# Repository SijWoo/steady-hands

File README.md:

# Introduction
This repo contains the src files and hardware for a wearable wrist band that treats chronic shaky hands.

## Background
Tremors make your hands or other parts of your body involuntarily move and shake. Severe cases can even make everday tasks difficult. This device is to let people from mild to severe cases regain control through the use of vibration feedback.

## How it works
Overloading the sensory nerves can surpress the involuntary movement. Vibration motors are implemented inside the wearable to constantly stimulate the nerves.

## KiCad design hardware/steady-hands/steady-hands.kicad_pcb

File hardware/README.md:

# Hardware
Descriptions and explanations

## Components
| Description | P/N |
| --- | --- |
| Microcontroller | STM32F411CE |
| Vibrating Motors | |
| IMU | BNO055 |

## Microcontroller
The STM32f411CE controls the vibration motors.

## Vibrating Motors
Small motors for phones are repurposed for this project. A transistor interface is needed to drive the required current.

## IMU
The BNO055 uses the I2C interface.

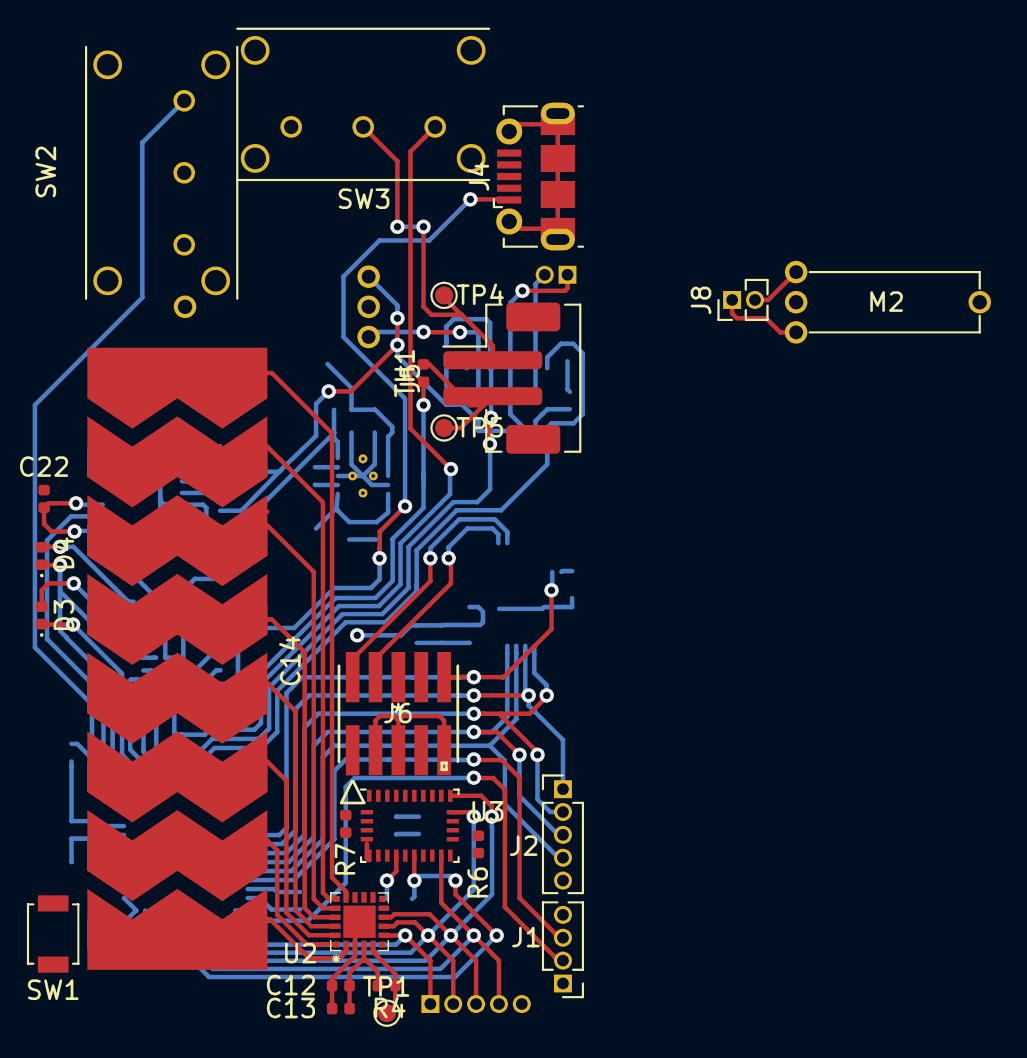
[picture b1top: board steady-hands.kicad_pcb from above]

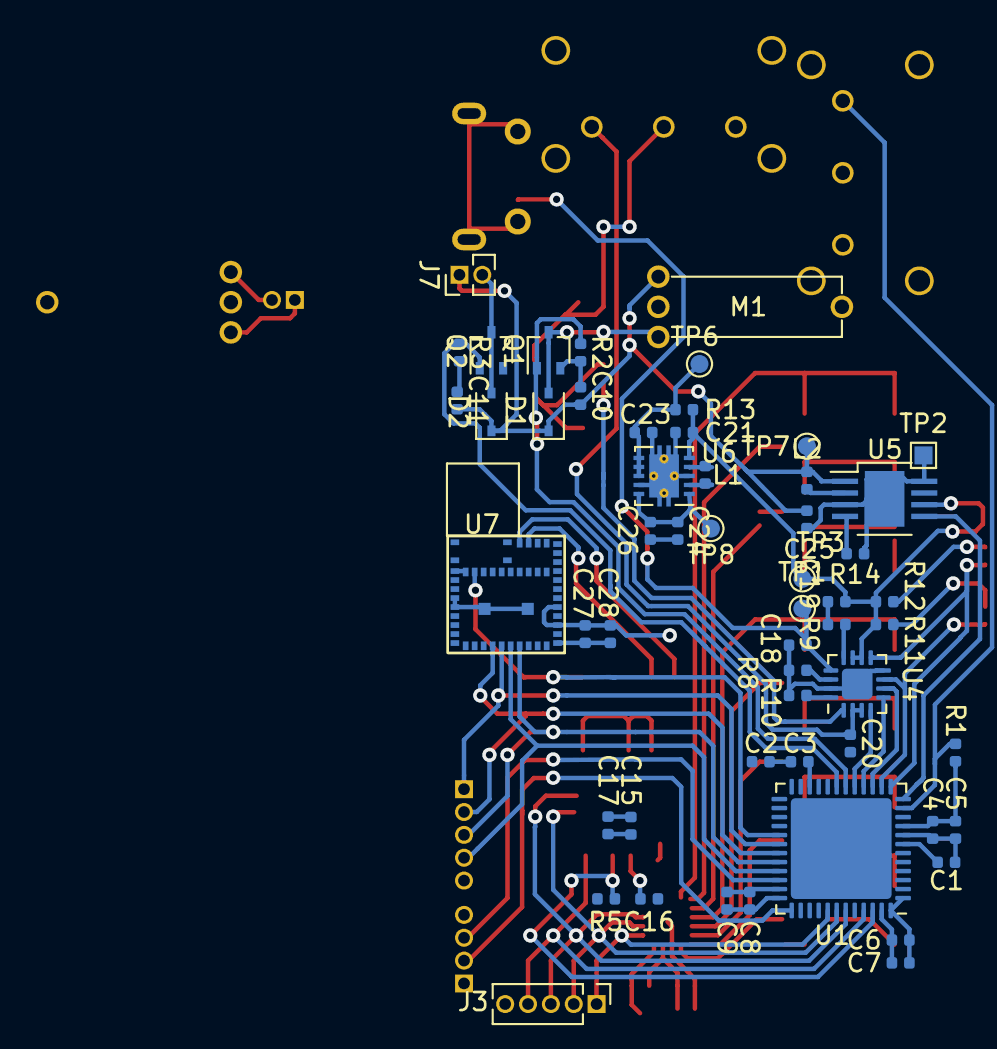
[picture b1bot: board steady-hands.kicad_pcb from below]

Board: 2 copper layers, 80 parts (55 on the bottom side), 62 nets.

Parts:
C1, C23: 0.1u; C_0402_1005Metric
C2, C4, C5, C6, C8, C17: 100n; C_0402_1005Metric
C3, C7, C19, C20, C22: 4.7u; C_0402_1005Metric
C9, C10, C11, C16, C18: 1u; C_0402_1005Metric
C12: 4.7uF; C_0402_1005Metric
C13: 0.1uF; C_0402_1005Metric
C14: CapSense_01x08; TouchSlider-8_35x10mm
C15: 120n; C_0402_1005Metric
C21, C24, C25, C26: 10u; C_0402_1005Metric
C27: 220n; C_0402_1005Metric
C28: 4.9u; C_0402_1005Metric
D1, D2: 1N4148WS; D_SOD-323
D3: Power; LED_0402_1005Metric
D4: Charge; LED_0402_1005Metric
J1: SWD; PinHeader_1x04_P1.27mm_Vertical
J2: UART; PinHeader_1x05_P1.27mm_Vertical
J3: I2C; PinHeader_1x05_P1.27mm_Vertical
J4: USB_B_Micro; USB_Micro-B_Molex-105017-0001
J5: BATT; JST_PH_B2B-PH-SM4-TB_1x02-1MP_P2.00mm_Vertical
J6: ARM_SWD; FTSH-105-01-L-DV-K
J7: MotorConn; PinHeader_1x02_P1.27mm_Vertical
J8: MotorConn1; PinHeader_1x02_P1.27mm_Vertical
L1, L2: 2.2u; L_0402_1005Metric
M1, M2: Motor_DC; 316040005
Q1, Q2: DMN2004WKQ; SOT-323_SC-70
R1, R2, R3, R4, R5, R6, R7: 10k; R_0402_1005Metric
R8, R9, R10: R; R_0402_1005Metric
R11, R12: 1.5k; R_0402_1005Metric
R13: 100; R_0402_1005Metric
R14: 28.7k; R_0402_1005Metric
SW1: RST_BTN; SW_SPST_B3U-1000P
SW2: SYNC_SW; EG1224
SW3: PWR_SW; EG1224
TH1: 10k; R_0402_1005Metric
TP1: VBus; TestPoint_Pad_D1.0mm
TP1#2: TestPoint; TestPoint_Pad_D1.0mm
TP2: GND; TestPoint_Pad_1.0x1.0mm
TP3: Vout; TestPoint_Pad_D1.0mm
TP4: +VBatt; TestPoint_Pad_D1.0mm
TP5: -VBatt; TestPoint_Pad_D1.0mm
TP6: VINA; TestPoint_Pad_D1.0mm
TP7: +1V3; TestPoint_Pad_D1.0mm
TP8: +3V3; TestPoint_Pad_D1.0mm
U1: STM32F411CEUx; QFN-48-1EP_7x7mm_P0.5mm_EP5.6x5.6mm
U2: CPT112S-A02-GM
U3: BNO055; LGA-28_5.2x3.8mm_P0.5mm
U4: BQ24075; QFN-16-1EP_3x3mm_P0.5mm_EP1.7x1.7mm
U5: TPS62841DGR; HVSSOP-8-1EP_3x3mm_P0.065mm_EP2.2x3.1mm_Mask1.35x1.65mm
U6: TPS63001; Texas_DRC0010J_ThermalVias
U7: BGM13S

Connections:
+1V3: C10.2, C11.2, C25.1, D1.1, D2.1, J7.1, L2.2, M1.1, TP7.1, U5.1
+3V3: C2.1, C4.1, C5.1, C6.1, C7.1, C8.1, C9.1, C12.1, C13.1, C15.1, C17.1, C24.1, C26.1, C27.1, C28.1, J1.1, J6.1, R1.1, R4.1, R5.1, R7.1, TP8.1, U1.1, U1.9, U1.24, U1.36, U1.48, U2.4, U3.3, U3.28, U6.1, U6.10, U7.22, U7.24
+5V: C18.1, J4.1, TP1.1, U4.13
+BATT: C19.1, C21.1, C22.1, R11.1, R12.1, R13.1, TP3.1, U4.10, U4.11, U5.6, U6.5
/Bluetooth/SWCLK: J6.4, U7.34
/Bluetooth/SWDIO: J6.2, U7.35
/Motors/+: J8.2, M2.1
/Motors/-: J8.1, M2.2
/Motors/V1-: D2.2, J7.2, Q2.3
/Motors/V-: D1.2, M1.2, Q1.3
/PA1: R1.2, SW2.1, U1.11
/PA2: U1.12, U5.5
/PA3: D4.1, U1.13, U4.9
/PA4: D3.1, U1.14, U4.7
/PA5: U1.15, U4.6
/PA6: U1.16, U4.5
/PA7: U1.17, U4.4
/PA8: J6.10, U1.29, U7.44
/PB5: J3.1, U1.41, U2.7
/PB8: J3.4, U1.45, U3.14
/PB9: R5.2, U1.46, U3.11
/Power Management/+VBATT: C20.1, SW3.1, U4.2, U4.3
/Power Management/-VBATT: J5.2, TH1.1, TP5.1
/SCL: J3.2, U1.42, U2.8, U3.19
/SDA: J3.3, U1.43, U2.9, U3.20
/SWCLK: J1.2, U1.37
/SWDIO: J1.3, U1.34
/TIM3_CH3: Q1.1, R2.1, U1.18
/TIM3_CH4: Q2.1, R3.1, U1.19
/UART1_CTS: J2.3, U1.32, U7.16
/UART1_RTS: J2.4, U1.33, U7.15
/UART1_RX: J2.2, U1.31, U7.13
/UART1_TX: J2.1, U1.30, U7.14
GND: C1.2, C2.2, C3.2, C4.2, C5.2, C6.2, C7.2, C8.2, C9.2, C12.2, C13.2, C15.2, C16.1, C17.2, C18.2, C19.2, C20.2, C21.2, C22.2, C23.2, C24.2, C25.2, C26.2, C27.2, C28.2, J1.4, J2.5, J3.5, J4.5, J6.3, J6.5, J6.9, R6.1, R8.2, R9.2, R10.2, R14.2, SW1.1, SW2.2, TP2.1, U1.8, U1.23, U1.35, U1.44, U1.47, U1.49, U2.3, U2.12, U2.21, U3.2, U3.5, U3.6, U3.15, U3.16, U3.18, U3.25, U4.8, U4.15, U4.17, U5.3, U5.8, U5.9, U6.3, U6.9, U6.11, U7.1, U7.4, U7.5, U7.20, U7.31, U7.45, U7.46, U7.47, U7.48, U7.49, U7.50, U7.51
GNDPWR: C10.1, C11.1, Q1.2, Q2.2, R2.2, R3.2
unnamed: C1.1, SW1.2, U1.7
unnamed: C3.1, U1.22
unnamed: C14.1, U2.2
unnamed: C14.2, U2.1
unnamed: C14.3, U2.20
unnamed: C14.4, U2.19
unnamed: C14.5, U2.18
unnamed: C14.6, U2.17
unnamed: C14.7, U2.16
unnamed: C14.8, U2.15
unnamed: C16.2, U3.9
unnamed: C23.1, R13.2, TP6.1, U6.6, U6.7, U6.8
unnamed: D3.2, R11.2
unnamed: D4.2, R12.2
unnamed: J5.1, SW3.2, TP4.1
unnamed: L1.1, U6.4
unnamed: L1.2, U6.2
unnamed: L2.1, U5.2
unnamed: R4.2, TP1#2.1, U2.5
unnamed: R6.2, U3.17
unnamed: R7.2, U3.4
unnamed: R8.1, U4.14
unnamed: R9.1, U4.12
unnamed: R10.1, U4.16
unnamed: R14.1, U5.4
unnamed: TH1.2, U4.1
unnamed: U7.2, U7.3

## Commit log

2020-04-23 Starts README.
2020-04-23 Fixes grammar in README
2020-04-24 Adds firmware starter project.
2020-04-25 Adds hardware readme
2020-04-25 Adds hardware descriptions in readme
2020-04-25 Adds apps and drivers
2020-06-18 Adds development board schematic
2020-06-21 Adds skeleton code of most src files
2020-06-21 Starter project compiles for stm32f411
2020-06-21 Adds test src files skeletons
2020-06-21 makefile compiles rtos code
2020-06-25 Creates prototypes for BSP_BNO055
2020-06-25 Creates prototypes for BSP_Motor
2020-06-25 Creates prototypes for Drv_Motor
2020-06-28 Edits development board schematic
2020-06-30 Updates HAL/LL I/O library
2020-07-03 Edits motor functions to control multiple motors
2020-07-03 Adds new components
2020-07-03 Adds symbol library
2020-07-03 Adds new BSP src files for new structure since some bsp modules are used multiple times in the drivers
2020-07-03 Removes gitignore for kicad libraries
2020-07-03 Adds documentation to bsp src files
2020-07-03 Adds missing bracket
2020-07-03 Feature/bsp structure (#6)
    * Adds new BSP src files for new structure since some bsp modules are used multiple times in the drivers
    * Adds new BSP src files for new structure since some bsp modules are used multiple times in the drivers
    * Adds new BSP src files for new structure since some bsp modules are used multiple times in the drivers
    * Adds documentation to bsp src files
    * Adds missing bracket
2020-07-03 Edits power management
2020-07-03 Adds ll i2c init
2020-07-03 Changes I2C init to HAL
2020-07-03 Finished bsp i2c
2020-07-03 Adds template bsp
2020-07-03 Changes test_motors file name
2020-07-03 Adds test for bsp_i2c:
2020-07-03 Changes intid_t and rstid_t to inputid_t and outputid_t, respectively
2020-07-03 Deletes template's bsp_gpio comment about stm32f411
2020-07-03 Changes Int and Rst to Input and Output to be more generic
2020-07-08 Adds BSP_GPIO_Init definition
2020-07-08 Corrects GPIO documentation
2020-07-08 Adds power management components
2020-07-09 Edits power management components
2020-07-09 Adds lib files
2020-07-09 Adds second motor components
2020-07-09 Completes schematic connections
2020-07-09 Edits gitignore to ignore temporary kicad files
2020-07-09 Deletes unnecessary kicad files
2020-07-10 Edits label names and switch configuration
2020-07-13 Updates files. Just making sure everything I didn't create any errors
2020-07-13 Deletes unnecessary files
2020-07-14 Adds footprints
2020-07-14 Adds IC footprints
2020-07-14 Adds all footprints to board
2020-07-17 Edits PCB layout
2020-07-18 Designs PCB layout of development board

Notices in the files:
parts and their libraries:
Copyright 2016 Accelerated Designs. All rights reserved.
